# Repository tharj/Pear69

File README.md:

# Pear69
An open source 65-ish% (69 diodes) keyboard running on KMK firmware designed mainly in KiCad.

I have previously made a couple of custom designs of keyboards, first an ergo and later a 65% board with a proprietary space split. With this, I mainly wanted to change firmware wise from ZMK to KMK for, in my opinion, easier modifications on the keymaps and functionality. At the same time I also wanted to include the possibility for different layouts, in case I end up building this for someone that doesn't want ANSI or split space.

## Basics

Default layout for me is ANSI with split space. It's not quite the normal 65% layout, as the top right corner houses the microcontroller running the keyboard. Keyboard layout editor(KLE) (http://www.keyboard-layout-editor.com/) Makes configuring the layout very easy, the extra keys for additional layouts are configured as well, for later use when we get to the actual PCB design. KLE lets you download the layout as a .json-file, that will be used in KiCad to make the actual switch positioning a breeze.

I designed the PCB for the Helios, which is a RP2040 based controller form 0xCB (https://github.com/0xCB-dev/0xCB-Helios). I also designed a quick and dirty case for 3D-printing that I used for the first board I put together. 

There is support for one encoder on the right hand side, as well as breakouts for an OLED screen (just under the controller, to cover the controller), and also breakouts for the extra pins that were not used in the key matrix, with 5v, 3.3v and ground. 

### BOM:
- A microcontroller (OxCB Helios)
- 70ish MX footprint switches of your choice 
- 70ish SMD diodes
- One EC11 rotary encoder (optional)
- One 128x32 OLED display (optional)
- Keycaps and a case are a nice bonus

## KiCad

For starters, KiCad is going to need a couple of things to make the design process a bit smoother:
- A library containing most of the symbols(for schematic) and footprints(for PCB) (https://github.com/ebastler/marbastlib)
- And a plugin to use the .json generated by KLE earlier (https://github.com/zykrah/kicad-kle-placer)

Design started with the schematic and figuring out the shape of the key matrix. Modern mechanical keyboard works by scanning a matrix of columns and rows, with diodes to prevent ghosting when used. There are a couple of different ways to configure the switches and diodes, I used diode direction "from column to row" here.

I won't go into detail on the basic function of the matrix scanning, as it's been covered multiple times in different places. Take a look at https://docs.qmk.fm/#/how_a_matrix_works?id=how-a-keyboard-matrix-works if you want to understand the whole process in more depth. In very basic level, pressing a key connects column and row pins on the controller. 

I ended up with a matrix of 7 columns and 10 rows, which allows for up to 70 keys, this leaves quite a few spare pins on the controller for an encoder and OLED and such.  Physical layout of course is not 7x10, so the PCB will end up with some tricky routing of traces.

Using a MX switch and a diode from the marbastlib we imported earlier, I created the 7x10 grid and ended up cutting it in half, to resemble the actual physical layout. With some tweaks to the grid due to the multiple layouts I ended up with a ready schematic for the key switches: 

From here you can assign a footprint of your choosing, I used a simple MX solder footprint. I tried to go with a hot swap socket at first, but the ANSI/ISO hybrid layout around the enter region got a bit too crowded and I downgraded to solder mount instead. 

After selecting the footprints for the switches and diodes (SOD123, a tiny SMD diode in this case), while in the PCB view, you can update the PCB from the schematic and get all your switches and diodes in to the PCB. 

### KLE placer plugin 

First, it's a good idea to check that the switch and diode footprints are on the right side of the PCB, i.e. in the right layer, in this case the back layer. Select all and flip to the appropriate side if needed. 

For the KLE placer plugin, the best way for me was to look for the switch and diode with index 0, and lay them out as you like, then the KLE plugin will not only put the switch footprints in the right locations, but also can move all the corresponding diodes according to the index 0 example you've given. KLE placer can also locate stabilizers where needed, but I ended up adding them by hand later, because of the split space needing multiple different stabilizer positions. 

When you run the KLE placer plugin, it places the switches exactly as shown in the KLE UI, so the additional layout keys have to be dragged to their place. This step requires some back and forth between the schematic and PCB, I ended up sharing some diodes between different keys in different layouts (and of course deleting the now extra diodes). Some switch orientations needed to be turned 90 to 180 degrees, to accommodate the different layout footprints. 

### Controller and routing

First I routed the traces for the rows and columns, mostly using one side of the PCB for rows and the other side for column traces, those got routed near the top right of the PCB, where the controller will be seated. Some layer changes needed to be made and the routing got a bit crowded in certain areas, mainly due to the difference in electrical matrix and physical layout of the keys.

I went with the Helios, which is a RP2040 based controller with c-usb, the footprint for it was also in the marbastlib library. After adding it to the schematic and to the PCB, I added tags for all the rows and columns, and started to figure out suitable pins on the controller. Having things actually connected in the schematic will enable nets in the PCB view, showing where everything needs to connect and further making it possible to check the validity of all connections with DCR (Design rules checker). It is much easier to sanity check your connections in the schematic than in the PCB, having an error pop up if you are missing a connection or there is some other violation, is very nice. 

As I had some spare pins, I added a OLED breakout below the controller and also an encoder(volume knob) on the right. Rest of the pins got broken out in the arrow cluster in the bottom right, just in case. 

I added the necessary stabilizers for the longer keys that use them, along with some mounting holes, allowing a tray mounting the PCB.

I also wanted a 'switch plate' for the keyboard, and simply took a copy of the KiCad project, deleted the unnecessary components and changed the switch footprints out to switch cut-outs from the marbastlib. Switch plate is just a PCB with no electrical function, to enable different mounting options. 

Using Fabrication outputs in KiCad, I exported the necessary gerber files and drill files, that the PCB manufacturer requires. I used JLCPCB and at least they have a guide for settings when exporting gerber files for manufacturing.

## Case and assembly

While I was waiting on the PCBs to be manufactured, I grabbed the plates from KiCad to Solidworks and started to design a case around them. I wanted something quick and dirty so I could build one board when the PCBs arrive. Nothing special in the case design, just top and bottom parts cut in half to get them to a printable size. 

When I actually got to printing, it took a few tries to get everything to line up with the PCBs. As a first time ABS printer I quickly learned that it likes to shrink while cooling. Scaling everything up by 0.7% was the final adjustment that made everything fit perfectly.

After the PCBs arrived, I soldered up a first prototype with some nice linear Alpaca switches I had lying around so I could get to figure out the firmware. There is plenty of videos going over actually building a custom keyboard, so I won't get into it here. 

## Setting up KMK

The basic setup for a custom board is quite straight forward. Find the proper release of CircuitPython for your board from https://circuitpython.org/downloads and flash the controller with the .UF2 by drag and drop to the drive according to the instructions(you have to be in the bootloader mode for the controller to accept UF2 files). 

After flashing the controller with the CircuitPython, installing KMK is really simple. They have good documentation for the first steps in http://kmkfw.io/docs/Getting_Started. I got KMK running very quickly with the instructions they provided. 

I figured it would be easier to understand what is going on by first making a version with hand configured keymaps etc. and ended up with a single code.py containing all info about the controller pins, diode orientation and coordinate mapping (which does the same thing as matrix transformation in ZMK, this just shifts the keys around so they are in the same order as in the physical layout) and also the encoder handling with keymaps for the whole matrix.

After a bit of tinkering I had a working config for the board with two layers containing most of the functionality I was going for at this point. 

### Peg

I also wanted to use the GUI built for KMK (https://peg.software/) and that required some modifications to the configs. After looking around in the Peg repo, it looked like the default structure was a kb.py for creating a python object containing the hardware config like pins and coordinate mapping and a main.py for keymaps, different modules(addons) like media keys. Peg also requires a layout.json, firstly for some configuration on what is found on the keyboard, device name and enabling or disabling certain features. The layout.json also contains the coordinates and sizes of keys for the graphical interface that is used with Peg. On top of those, I also have a boot.py for hiding the storage device when connecting among other things.

There is some issues with compatibility when using latest stock KMK on CircuitPython and Peg together. These would be solved by using a custom firmware on the controller from boardsource called boardsource-python. It is only available for a handful of controllers at the moment, and the Helios is not among them, at least yet. Building bs-python for a new controller is a bit out of my comfort zone for now.

The problem with the current setup is that when the layout in Peg includes a momentary layer change (MO(#)), Peg includes imports to modules that are not found in the current KMK repo, but have been moved to another module with different name. I worked around this by grabbing the "missing" modtap.py from an old fork of KMK and while it's not a elegant solution, it works for now. The real fix would be to port bs-python for the particular controller, as bs-python seems to include the same version of KMK that Peg is configured with, thus avoiding version to version incompability.

## TBD

I still have the OLED to install and configure. There also were some oversights in the first version of the PCBs that I ordered, that have since been fixed. I only had one of the Helios controllers and it is out of stock in EU right now, so depending when they restock, I might end up changing it out to something with Bluetooth.

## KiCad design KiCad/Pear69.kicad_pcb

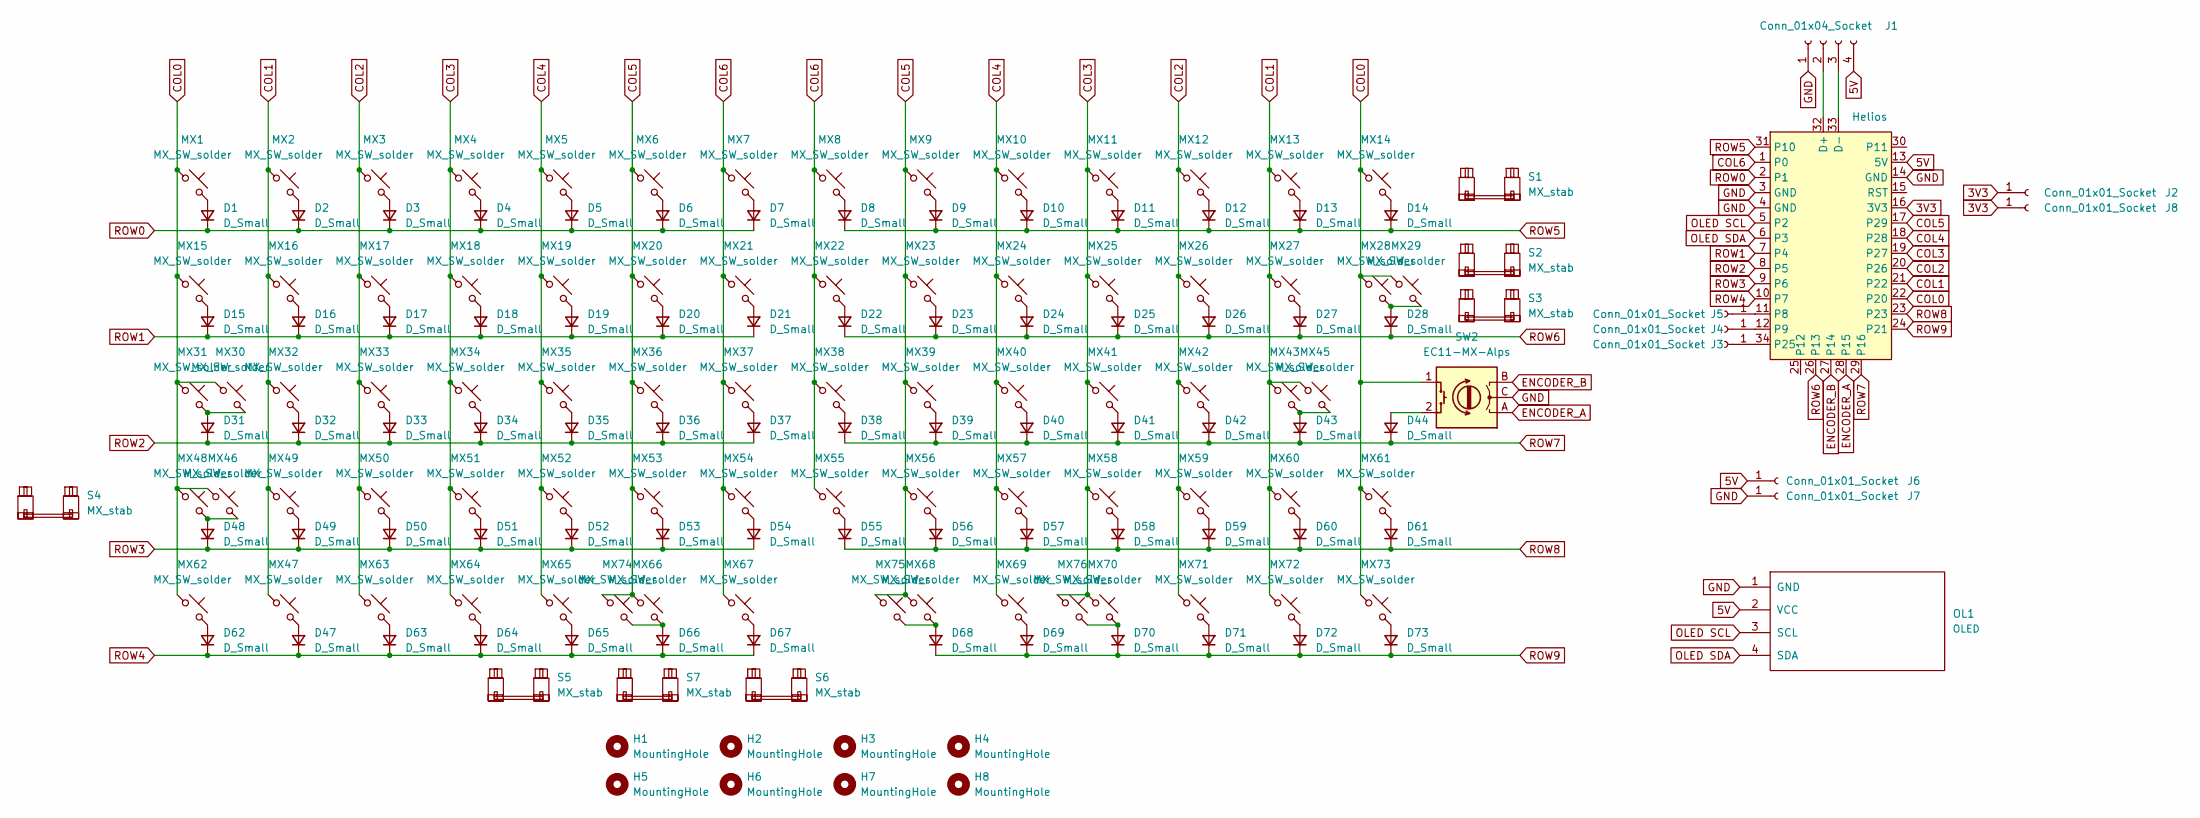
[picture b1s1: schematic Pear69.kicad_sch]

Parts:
D1, D2, D3, D4, D5, D6, D7, D8, D9, D10, D11, D12, D13, D14, D15, D16, D17, D18, D19, D20, D21, D22, D23, D24, D25, D26, D27, D28, D31, D32, D33, D34, D35, D36, D37, D38, D39, D40, D41, D42, D43, D44, D47, D48, D49, D50, D51, D52, D53, D54, D55, D56, D57, D58, D59, D60, D61, D62, D63, D64, D65, D66, D67, D68, D69, D70, D71, D72, D73: D_Small; D_SOD-123_RotatedSS
H1, H2, H3, H4, H5, H6, H7, H8: MountingHole; MountingHole_2.7mm_M2.5
J1: Conn_01x04_Socket; PinHeader_1x04_P2.54mm_Vertical
J2, J3, J4, J5, J6, J7, J8: Conn_01x01_Socket; PinHeader_1x01_P2.54mm_Vertical_NOSS
MX1, MX2, MX3, MX4, MX5, MX6, MX7, MX8, MX9, MX10, MX11, MX12, MX13, MX14, MX16, MX17, MX18, MX19, MX20, MX21, MX22, MX23, MX24, MX25, MX26, MX27, MX29, MX32, MX33, MX34, MX35, MX36, MX37, MX38, MX39, MX40, MX41, MX42, MX43, MX45, MX47, MX48, MX49, MX50, MX51, MX52, MX53, MX54, MX55, MX56, MX57, MX58, MX60, MX61, MX65, MX67, MX68, MX69, MX70, MX71, MX72, MX73, MX74: MX_SW_solder; SW_MX_1u
MX15, MX28, MX75, MX76: MX_SW_solder; SW_MX_1.5u
MX30: MX_SW_solder; SW_MX_1.75u_STP_1.25
MX31, MX59: MX_SW_solder; SW_MX_1.75u
MX46, MX62, MX63, MX64, MX66: MX_SW_solder; SW_MX_1.25u
OL1: OLED; I2C_Breakout
S1: MX_stab; STAB_MX_P_2u
S2, S4, S6: MX_stab; STAB_MX_P_2.25u
S3: MX_stab; STAB_MX_P_ISO
S5: MX_stab; STAB_MX_P_2.75u
S7: MX_stab; STAB_MX_P_6.25u
SW2: EC11-MX-Alps
U1: Helios; Helios_AH_USBup

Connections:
3V3: J2.1, J8.1, U1.16 (3V3)
5V: J1.4, J6.1, OL1.2 (VCC), U1.13 (5V)
COL0: MX1.1, MX14.1, MX15.1, MX28.1, MX29.1, MX30.1, MX31.1, MX46.1, MX48.1, MX61.1, MX62.1, MX73.1, SW2.1, U1.22 (P20)
COL1: MX2.1, MX13.1, MX16.1, MX27.1, MX32.1, MX43.1, MX45.1, MX47.1, MX49.1, MX60.1, MX72.1, U1.21 (P22)
COL2: MX3.1, MX12.1, MX17.1, MX26.1, MX33.1, MX42.1, MX50.1, MX59.1, MX63.1, MX71.1, U1.20 (P26)
COL3: MX4.1, MX11.1, MX18.1, MX25.1, MX34.1, MX41.1, MX51.1, MX58.1, MX64.1, MX70.1, MX76.1, U1.19 (P27)
COL4: MX5.1, MX10.1, MX19.1, MX24.1, MX35.1, MX40.1, MX52.1, MX57.1, MX65.1, MX69.1, U1.18 (P28)
COL5: MX6.1, MX9.1, MX20.1, MX23.1, MX36.1, MX39.1, MX53.1, MX56.1, MX66.1, MX68.1, MX74.1, MX75.1, U1.17 (P29)
COL6: MX7.1, MX8.1, MX21.1, MX22.1, MX37.1, MX38.1, MX54.1, MX55.1, MX67.1, U1.1 (P0)
ENCODER_A: SW2.A, U1.28 (P15)
ENCODER_B: SW2.B, U1.27 (P14)
GND: J1.1, J7.1, OL1.1 (GND), SW2.C, U1.3 (GND), U1.4 (GND), U1.14 (GND)
unnamed: D1.2 (A), MX1.2
unnamed: D2.2 (A), MX2.2
unnamed: D3.2 (A), MX3.2
unnamed: D4.2 (A), MX4.2
unnamed: D5.2 (A), MX5.2
unnamed: D6.2 (A), MX6.2
unnamed: D7.2 (A), MX7.2
unnamed: D8.2 (A), MX8.2
unnamed: D9.2 (A), MX9.2
unnamed: D10.2 (A), MX10.2
unnamed: D11.2 (A), MX11.2
unnamed: D12.2 (A), MX12.2
unnamed: D13.2 (A), MX13.2
unnamed: D14.2 (A), MX14.2
unnamed: D15.2 (A), MX15.2
unnamed: D16.2 (A), MX16.2
unnamed: D17.2 (A), MX17.2
unnamed: D18.2 (A), MX18.2
unnamed: D19.2 (A), MX19.2
unnamed: D20.2 (A), MX20.2
unnamed: D21.2 (A), MX21.2
unnamed: D22.2 (A), MX22.2
unnamed: D23.2 (A), MX23.2
unnamed: D24.2 (A), MX24.2
unnamed: D25.2 (A), MX25.2
unnamed: D26.2 (A), MX26.2
unnamed: D27.2 (A), MX27.2
unnamed: D28.2 (A), MX28.2, MX29.2
unnamed: D31.2 (A), MX30.2, MX31.2
unnamed: D32.2 (A), MX32.2
unnamed: D33.2 (A), MX33.2
unnamed: D34.2 (A), MX34.2
unnamed: D35.2 (A), MX35.2
unnamed: D36.2 (A), MX36.2
unnamed: D37.2 (A), MX37.2
unnamed: D38.2 (A), MX38.2
unnamed: D39.2 (A), MX39.2
unnamed: D40.2 (A), MX40.2
unnamed: D41.2 (A), MX41.2
unnamed: D42.2 (A), MX42.2
unnamed: D43.2 (A), MX43.2, MX45.2
unnamed: D44.2 (A), SW2.2
unnamed: D47.2 (A), MX47.2
unnamed: D48.2 (A), MX46.2, MX48.2
unnamed: D49.2 (A), MX49.2
unnamed: D50.2 (A), MX50.2
unnamed: D51.2 (A), MX51.2
unnamed: D52.2 (A), MX52.2
unnamed: D53.2 (A), MX53.2
unnamed: D54.2 (A), MX54.2
unnamed: D55.2 (A), MX55.2
unnamed: D56.2 (A), MX56.2
unnamed: D57.2 (A), MX57.2
unnamed: D58.2 (A), MX58.2
unnamed: D59.2 (A), MX59.2
unnamed: D60.2 (A), MX60.2
unnamed: D61.2 (A), MX61.2
unnamed: D62.2 (A), MX62.2
unnamed: D63.2 (A), MX63.2
unnamed: D64.2 (A), MX64.2
unnamed: D65.2 (A), MX65.2
unnamed: D66.2 (A), MX66.2, MX74.2
unnamed: D67.2 (A), MX67.2
unnamed: D68.2 (A), MX68.2, MX75.2
unnamed: D69.2 (A), MX69.2
unnamed: D70.2 (A), MX70.2, MX76.2
unnamed: D71.2 (A), MX71.2
unnamed: D72.2 (A), MX72.2
unnamed: D73.2 (A), MX73.2
unnamed: J1.2, U1.32 (D+)
unnamed: J1.3, U1.33 (D-)
unnamed: J3.1, U1.34 (P25)
unnamed: J4.1, U1.12 (P9)
unnamed: J5.1, U1.11 (P8)
OLED SCL: OL1.3 (SCL), U1.5 (P2)
OLED SDA: OL1.4 (SDA), U1.6 (P3)
ROW0: D1.1 (K), D2.1 (K), D3.1 (K), D4.1 (K), D5.1 (K), D6.1 (K), D7.1 (K), U1.2 (P1)
ROW1: D15.1 (K), D16.1 (K), D17.1 (K), D18.1 (K), D19.1 (K), D20.1 (K), D21.1 (K), U1.7 (P4)
ROW2: D31.1 (K), D32.1 (K), D33.1 (K), D34.1 (K), D35.1 (K), D36.1 (K), D37.1 (K), U1.8 (P5)
ROW3: D48.1 (K), D49.1 (K), D50.1 (K), D51.1 (K), D52.1 (K), D53.1 (K), D54.1 (K), U1.9 (P6)
ROW4: D47.1 (K), D62.1 (K), D63.1 (K), D64.1 (K), D65.1 (K), D66.1 (K), D67.1 (K), U1.10 (P7)
ROW5: D8.1 (K), D9.1 (K), D10.1 (K), D11.1 (K), D12.1 (K), D13.1 (K), D14.1 (K), U1.31 (P10)
ROW6: D22.1 (K), D23.1 (K), D24.1 (K), D25.1 (K), D26.1 (K), D27.1 (K), D28.1 (K), U1.26 (P13)
ROW7: D38.1 (K), D39.1 (K), D40.1 (K), D41.1 (K), D42.1 (K), D43.1 (K), D44.1 (K), U1.29 (P16)
ROW8: D55.1 (K), D56.1 (K), D57.1 (K), D58.1 (K), D59.1 (K), D60.1 (K), D61.1 (K), U1.23
ROW9: D68.1 (K), D69.1 (K), D70.1 (K), D71.1 (K), D72.1 (K), D73.1 (K), U1.24 (P21)

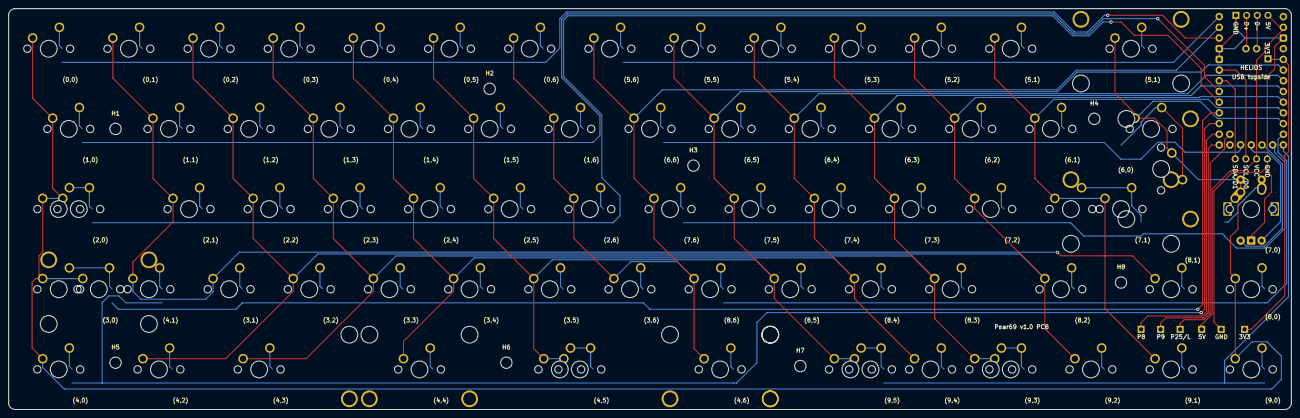
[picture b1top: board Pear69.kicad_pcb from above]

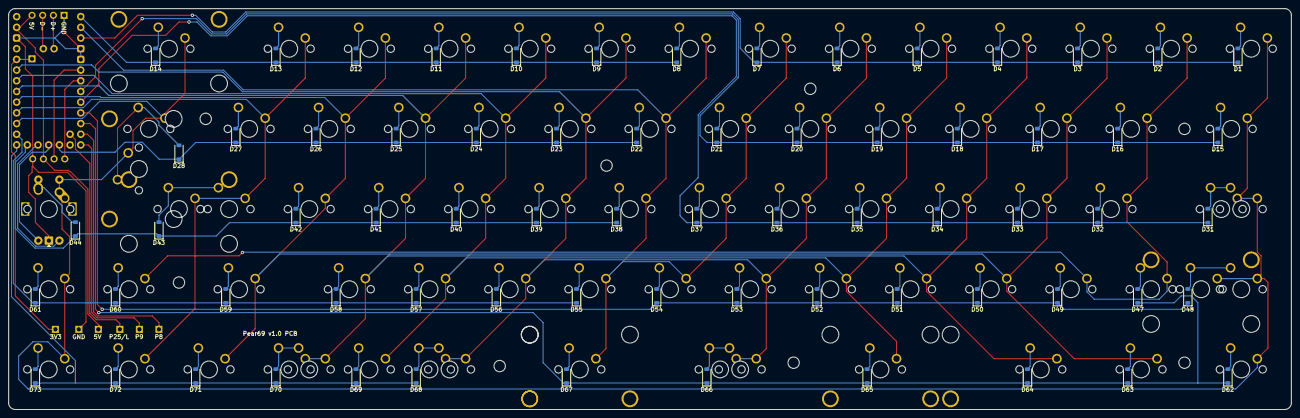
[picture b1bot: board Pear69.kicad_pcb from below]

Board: 2 copper layers, 304.8 x 95.3 mm, 170 parts (69 on the bottom side), 98 nets.

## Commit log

2024-01-15 Initial commit: Create repo and files for Pear69
2024-01-15 Add .gitignore
2024-03-28 Upload files
2024-03-28 Delete KMK/main.py
    Clean up directory
2024-03-28 Update README.md
    Add images
